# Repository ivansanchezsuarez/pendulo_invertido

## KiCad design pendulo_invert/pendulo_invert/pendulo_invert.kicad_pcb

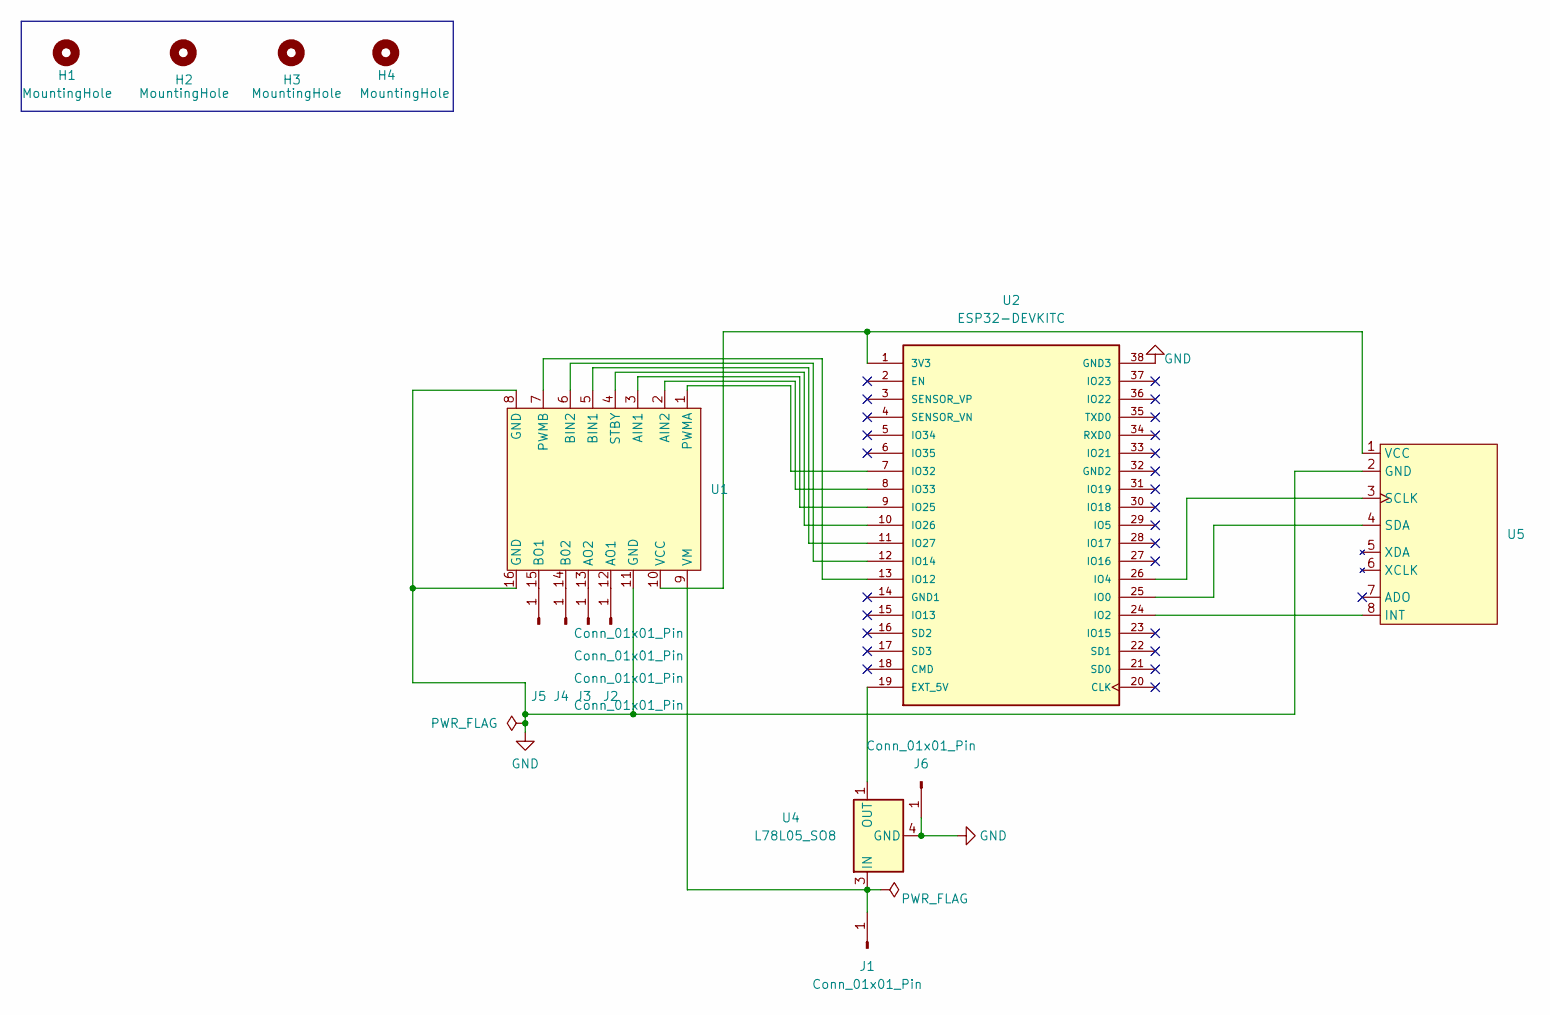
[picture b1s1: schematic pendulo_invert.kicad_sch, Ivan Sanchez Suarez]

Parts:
H1, H2, H3, H4: MountingHole; MountingHole_3mm
J1, J2, J3, J4, J5, J6: Conn_01x01_Pin; 1_524
U1: driver
U2: ESP32-DEVKITC; MODULE_ESP32-DEVKITC; PARTREV N/A
U4: L78L05_SO8; D2PAK-STB35NF10T4
U5: MPU

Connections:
GND: J6.1, U1.8 (GND), U1.11 (GND), U1.16 (GND), U2.38 (GND3), U4.4 (GND), U5.2 (GND)
unnamed: J1.1, U1.9 (VM), U4.3 (IN)
unnamed: J2.1, U1.12 (AO1)
unnamed: J3.1, U1.13 (AO2)
unnamed: J4.1, U1.14 (B02)
unnamed: J5.1, U1.15 (BO1)
unnamed: U1.3 (AIN1), U2.9 (IO25)
unnamed: U1.2 (AIN2), U2.8 (IO33)
unnamed: U1.5 (BIN1), U2.11 (IO27)
unnamed: U1.6 (BIN2), U2.12 (IO14)
unnamed: U1.1 (PWMA), U2.7 (IO32)
unnamed: U1.7 (PWMB), U2.13 (IO12)
unnamed: U1.4 (STBY), U2.10 (IO26)
unnamed: U1.10 (VCC), U2.1 (3V3), U5.1 (VCC)
unnamed: U2.19 (EXT_5V), U4.1 (OUT)
unnamed: U2.25 (IO0), U5.4 (SDA)
unnamed: U2.24 (IO2), U5.8 (INT)
unnamed: U2.26 (IO4), U5.3 (SCLK)

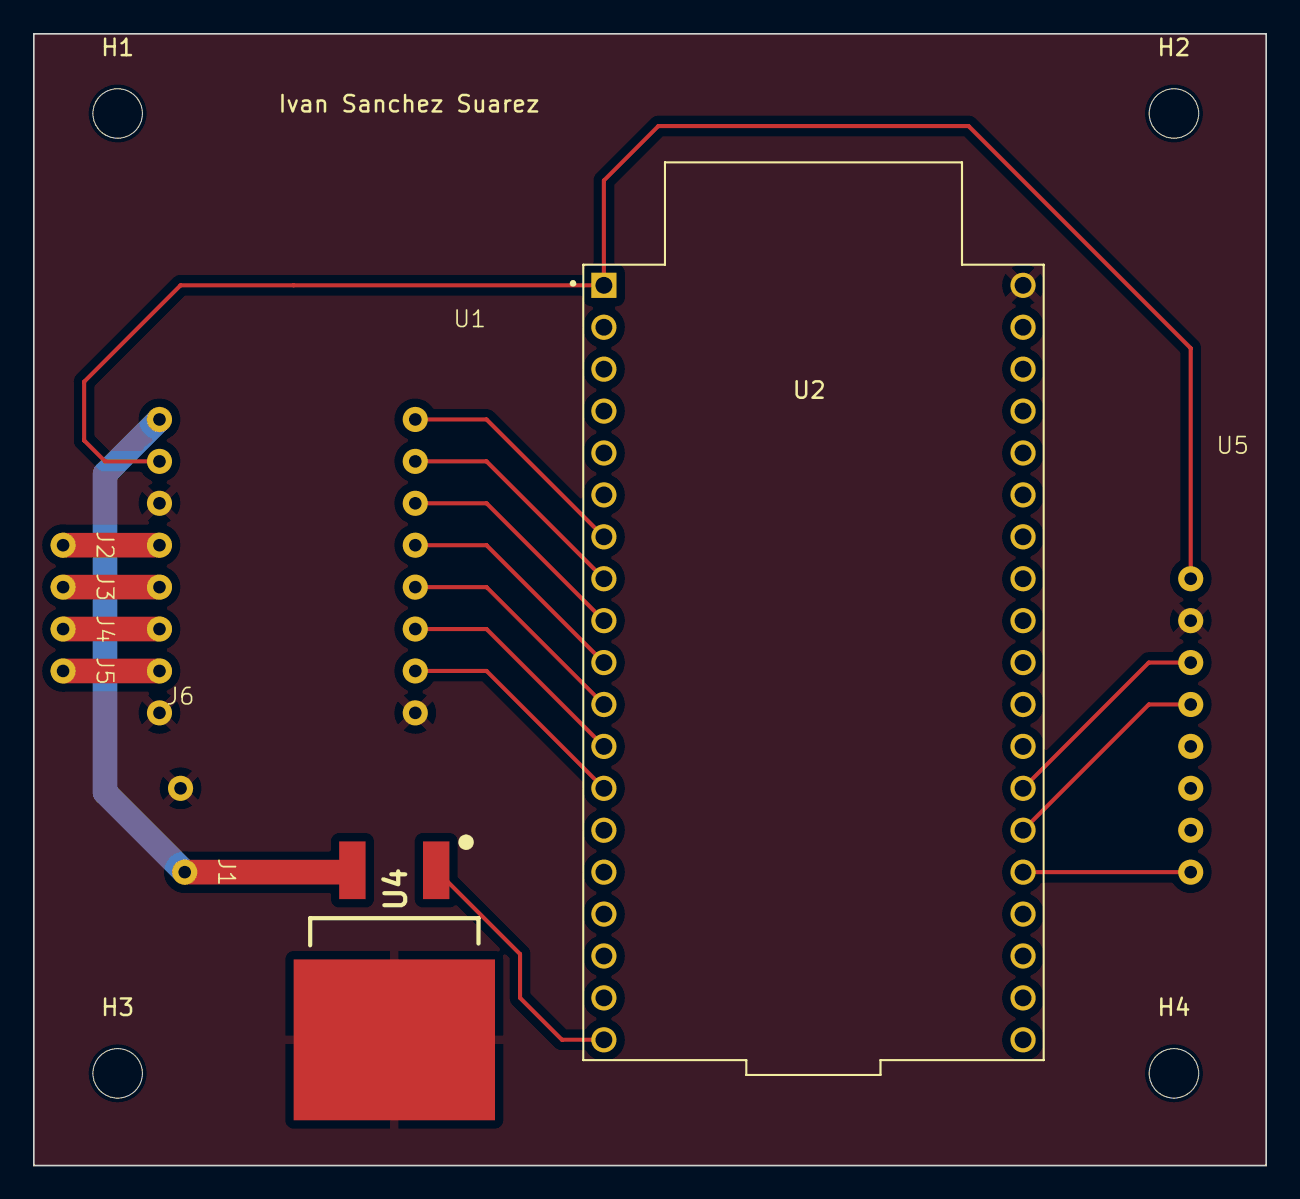
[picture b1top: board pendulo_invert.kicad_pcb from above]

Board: 2 copper layers, 74.7 x 68.6 mm, 14 parts (0 on the bottom side), 18 nets.

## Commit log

2024-03-27 Create pendulo_invertido
